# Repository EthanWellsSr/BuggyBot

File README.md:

# BuggyBot

University of Houston–Clear Lake (UHCL) Senior Project, CENG 4265. The course
deliverables use the project title **Self Driving RC Car**; BuggyBot is the
repository and vehicle name.

BuggyBot is an autonomous car project intended to follow a controlled course and obey
traffic signs. The fall scope is a stationary sign-recognition system; the
spring scope is the autonomous vehicle.

## Current state

- The bench platform uses a Raspberry Pi Compute Module 5 (CM5) on its IO Board,
  booting Raspberry Pi OS Lite from an M.2 NVMe SSD. USB Wi-Fi supplies network
  access because this CM5 Lite has no onboard wireless.
- [`Model Training/OpenCV/pi_sign_detection_demo.py`](Model%20Training/OpenCV/)
  is the live sign demo on the CM5. It finds sign regions with OpenCV,
  classifies them with the combined model, and shows the confirmed sign on the
  LCD. In the final test, 60 of 60 LCD outputs were correct (10 printed sign
  classes, 3 times each over two runs, one room).
- [`Hardware/scripts/test_components.py`](Hardware/scripts/test_components.py)
  and [`Hardware/scripts/stress_test.py`](Hardware/scripts/stress_test.py) are
  the hardware integration tests: each device on its own, then
  everything at once. On 10/28 all seven stages of the original combined test passed
  on the Cokoino HAT (pins, I²C, line sensors, IMU, motors, sign pipeline, and a
  120 s stress run with everything at once), powered from the Pi with the wheels
  off the ground. On 11/02 the 120 s stress run passed again with the motors on
  real power (a 9 V bench supply into the Cokoino HAT): no under-voltage, no I²C
  or line-sensor noise, and 30 fps. For the Semester 1 demo, Ethan Bishop's own
  battery runs the CM5, camera, LCD, and travel router, so the demo is mobile
  and reachable over SSH. Motors on battery power and a loaded drivetrain are
  untested. Reports are
  in [`Hardware/integration_reports/`](Hardware/integration_reports/). Nothing
  drives the vehicle yet.
- TensorFlow classifiers have been trained on GTSRB, LISA, Mapillary, and a
  combined LISA+Mapillary dataset. Their models and results are in this repo.
- A ROS 2 node architecture for the vehicle (camera, sign detector, line sensor,
  IMU, behavior, motor driver, LCD, teleop) has been drafted. ROS 2 is installed
  under WSL on a development machine. A preliminary ROS 2 version of the sign
  pipeline (camera, sign classifier, and LCD nodes) runs in Docker on a
  development machine; it is not in this repository and has not run on the CM5.

## Hardware

- **Compute and storage:** Raspberry Pi CM5 (4 GB Lite), CM5 IO Board, M.2 NVMe
- **Networking:** USB Wi-Fi dongle for headless SSH
- **Vision and sensing:** Camera Module 3, ICM-20948 IMU (the HC-SR04 ultrasonic sensor is no longer used)
- **Course sensing:** TCRT5000 IR line sensors (received); a line-sensor script that
  reads the left (GPIO20) and right (GPIO21) sensors is in `Hardware/scripts/Line Sensors.py`
- **Output and motion:** I²C LCD; two motor-controller HATs are supported: the
  Waveshare Motor Driver HAT (2WD, I²C) and the Cokoino 4WD Robot HAT (GPIO).
  Vehicle motor control is being developed
- **Chassis:** EMOZNY Emo smart robot car chassis kit (2 DC gear motors with
  speed encoders, battery box) has been received
- **Custom PCB:** a KiCad carrier-board design, derived from the CM5 IO Board, is
  complete in [`Hardware/BuggyBot KiCAD/`](Hardware/BuggyBot%20KiCAD/), with
  Gerber, BOM, and pick-and-place files (11/03). PCBWay quoted $583 to
  manufacture it, so it will not be made; BuggyBot uses the stock CM5 IO Board

The [parts list](Hardware/partslist.md) records purchase and availability
status. Wiring references and hardware test scripts are in [`Hardware/`](Hardware/);
see its [README](Hardware/README.md).

## Traffic-sign models

The image classifiers use 32×32 sign crops. On the CM5, the live demo in
[`Model Training/OpenCV/`](Model%20Training/OpenCV/README.md) locates signs in
each camera frame, crops them without using the known class, and runs the
combined TFLite model on each crop.

| Dataset and model | Classes | Prepared crops | Held-out result | Status |
| --- | ---: | ---: | --- | --- |
| GTSRB, German signs | 43 | See [training guide](Model%20Training/README.md) | 95.79% top-1 on 12,630 test images | Model and evaluation committed |
| LISA, selected US signs | 12 | 6,097 | 89.90% top-1 on 584 test crops | Model and report committed |
| Mapillary, mapped to the same 12 classes | 12 | 3,449 | 92.59% top-1 on 432 test crops | Model and report committed |
| Combined LISA+Mapillary | 12 | 9,546 | 99.31% top-1 on 1,016 combined test crops | Model, training report, and same-set comparison committed |

The separate LISA and Mapillary percentages use **different test sets** and do
not rank those models. The [same-set comparison](Model%20Training/reports/combined_model_comparison.md)
evaluates all three US-sign models on the 1,016 combined test crops. The
combined set preserves each source's split but does not establish physical-sign
independence across datasets. The Mapillary test set has only two speed-limit-65
crops.

On BuggyBot's own camera, the combined model classified **all 329** cropped
photos of the printed [sign cards](Sign%20Cards/README.md) correctly (10
classes, three lighting conditions, about 30 distinct setups). The LISA and
Mapillary models scored 47.7% and 79.9%. These crops were placed with
knowledge of each sign's class. Through the car's own detector (the live
demo), 60 of 60 LCD outputs were correct in one room; distance, angle, other
lighting are still unmeasured; CM5 inference averaged 1.9 ms per crop (36 fps). See the [model training guide](Model%20Training/README.md) for the
scripts, preparation steps, and detailed results.

## Team

- Ethan Wells (Group Leader)
- Alexis Perez
- Ethan Bishop
- Abigail Duran

**Faculty advisor:** Dr. Nguyen · **TA:** Ruben Ramirez

## Repository layout

| Path | Contents |
| --- | --- |
| `Proposal/` | Project proposal and Gantt charts |
| `Semester 1 Deliverables/` | Final Semester 1 deliverables: poster, final presentation, Project Report, and Technical Paper |
| `Weekly Reports/` | Rolling report and presentation, source slides, build scripts, and frozen weekly deliverables |
| `Hardware/` | Parts list, wiring references, hardware test scripts, integration test reports, and the KiCad custom-PCB project |
| `Model Training/` | GTSRB, LISA, Mapillary, and combined-data preparation, training, evaluation, and reports; the live Pi sign demo in `OpenCV/`; downloaded datasets are Git ignored |
| `Sign Cards/` | Printable 3 x 5 inch cards for the 12 U.S. sign classes, a US Letter print sheet, and cropped camera test photos |
| `Learning/` | Self-directed learning side-quests, separate from the main project |
| `setup.sh` | Installs Git, Python, pip, and venv on your development computer |
| `Hardware/setup.sh` | Installs Picamera2, OpenCV, NumPy, SMBus, GPIOZero, and the LiteRT venv on BuggyBot (the CM5) |
| `AGENTS.md` | Working agreements for AI assistants used on this repo |
| `.github/` | GitHub Actions CI, run on every push: Python scripts compile, `ruff` bug lint, sign-demo regression on the 329 test crops, integration-test pin map for both motor HATs, and Markdown link check (helper scripts in `.github/scripts/`) |

### Weekly reports

Weekly reports and the presentation deck are built from `Weekly Reports/`;
see [`Weekly Reports/context.md`](Weekly%20Reports/context.md) for the build
and format guide, and [`slides/README.md`](Weekly%20Reports/slides/README.md)
for how each person edits their own slides.

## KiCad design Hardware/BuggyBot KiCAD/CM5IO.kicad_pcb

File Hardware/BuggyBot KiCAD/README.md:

# BuggyBot KiCad Hardware Files

This folder contains the KiCad design files used for the BuggyBot senior capstone project.

The design started from the Raspberry Pi Compute Module 5 IO Board files and was modified into the custom BuggyBot carrier PCB. Abigail Duran completed the layout and generated the manufacturing files in Week 11 (11/03/2026), and Ethan Wells gave final approval to send it for manufacturing. After PCBWay quoted $583, the team decided not to manufacture it.

## Main Project Files

- `CM5IO.kicad_pro`  
  Main KiCad project file. Open this file first to load the complete project.

- `CM5IO.kicad_sch`  
  Main schematic, inherited from the CM5 IO Board.

- `CM5IO.kicad_pcb`  
  PCB layout for BuggyBot: 4 layers, 1.6 mm FR-4. Earlier layouts,
  including the 10/23 redesign file, are in Git history.

- `CM5IO.kicad_sym`  
  Custom symbol library used by the project.

## Additional Schematic Sheets

- `CM5_GPIO.kicad_sch`  
  GPIO-related circuitry, including the BuggyBot additions: 4-pin quick-connect
  ports for the IMU (J3) and the LCD (J4).

- `CM5_HighSpeed.kicad_sch`  
  High-speed interfaces and related circuitry.

- `PCIe-M2.kicad_sch`  
  PCIe and M.2 circuitry.

## Libraries

- `CM5IO.pretty/`  
  Custom KiCad footprint library.

- `Image.pretty/`  
  BuggyBot ladybug logo footprints for the silkscreen.

- `CM5IO.3dshapes/`  
  3D models used by PCB footprints.

- `fp-lib-table`  
  KiCad footprint library configuration.

- `sym-lib-table`  
  KiCad symbol library configuration.

## Manufacturing Files (`PCBWay/`)

- `Gerbers/`  
  Gerber files for each copper, mask, paste, silkscreen, and edge-cut layer,
  the plated and non-plated drill files, and the Gerber job file.

- `Gerbers.zip`  
  The same Gerber and drill files in one archive for upload to the board house.

- `Gerbers/IMPEDANCE_CONTROL.txt`  
  Stackup and controlled-impedance requirements for the board house
  (100 Ω and 90 Ω differential pairs, 50 Ω single-ended).

- `BuggyBotBOM.xlsx`  
  Bill of materials for the BuggyBot board.

- `CM5IO-all-pos.csv`  
  Pick-and-place (component position) file for assembly.

## Other Files

- `CM5IOBOM.txt`  
  Bill of Materials from the original CM5 IO Board design.

## Opening the Project

1. Install KiCad 10 or a compatible newer version.
2. Clone or download the BuggyBot repository.
3. Navigate to:

   `Hardware/BuggyBot KiCAD`

4. Open:

   `CM5IO.kicad_pro`

Opening the `.kicad_pro` file should load the schematic, PCB, and associated project libraries.

## Project Purpose

These files are the final design for BuggyBot's custom PCB. PCBWay quoted $583 to manufacture and assemble it (after a discount), which the team judged not financially feasible. The board will not be manufactured; BuggyBot uses the stock CM5 IO Board.

The original CM5 IO Board contains some different hardware than BuggyBot requires. In October 2026 the team reviewed which CM5 support circuitry and interfaces to keep, removing the second HDMI port, the second camera/display connector, and the microSD slot, and added quick-connect headers for BuggyBot's sensors and display: the IMU (J3, 10/14), the LCD (J4, 10/22), and the two line sensors (J6 and J7, 10/23). The component checklist from that review is not committed to this repository.

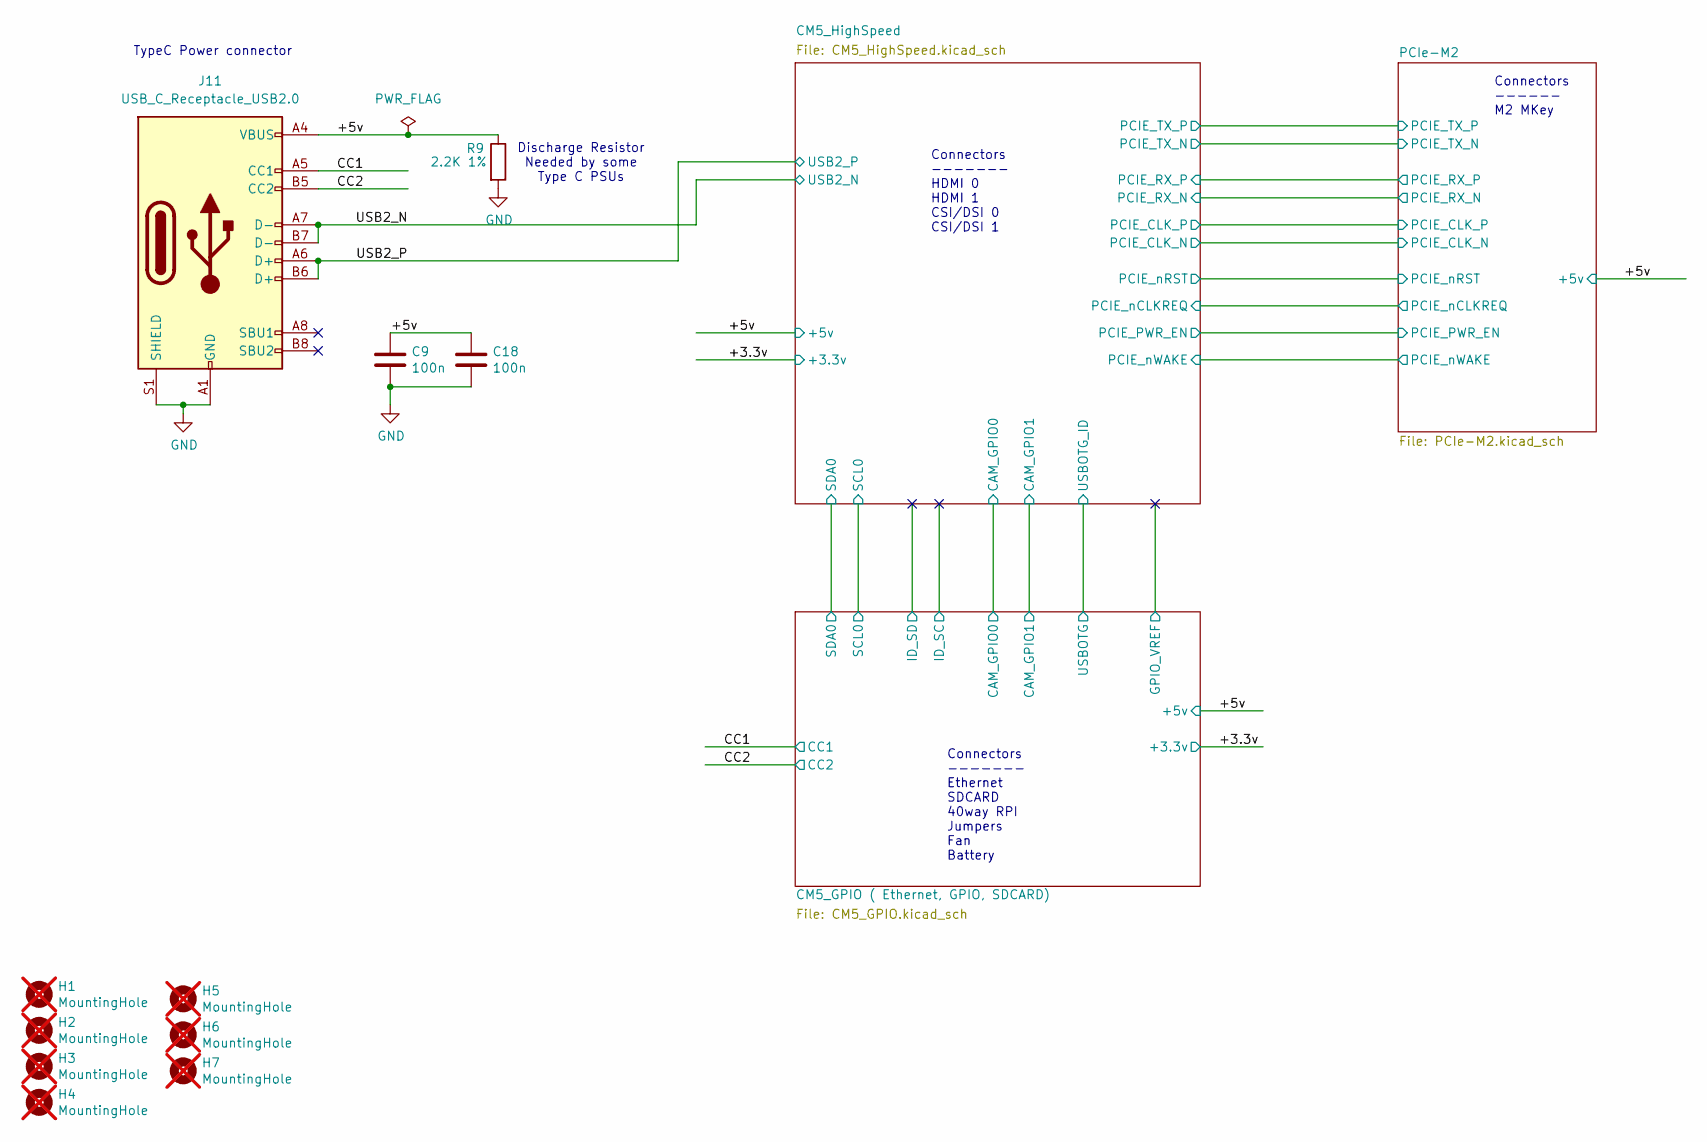
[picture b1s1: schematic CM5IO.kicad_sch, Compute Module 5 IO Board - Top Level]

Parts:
C9, C18: 100n; C_0402_1005Metric; Part Description 0.1uF 10% 16V Ceramic Capacitor X7R 040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
H1, H2, H3, H4, H5, H6, H7: MountingHole; MountingHole_2.7mm_M2.5_DIN965; Part Description M2.5 mounting hole; not fitted
J11: USB_C_Receptacle_USB2.0; USB_C_Receptacle_GCT_USB4105-xx-A_16P_TopMnt_Horizontal; Part Description USBC USB2 data and power connector
R9: 2.2K 1%; R_0402_1005Metric; Part Description Resistor 2.2K M1005 1% 63mW

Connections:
/+5v: C9.1, C18.1, J11.A4 (VBUS), J11.A9 (VBUS), J11.B4 (VBUS), J11.B9 (VBUS), R9.1; also elsewhere on the board
/CC1: J11.A5 (CC1); also elsewhere on the board
/CC2: J11.B5 (CC2); also elsewhere on the board
/USB2_N: J11.A7 (D-), J11.B7 (D-); also elsewhere on the board
/USB2_P: J11.A6 (D+), J11.B6 (D+); also elsewhere on the board
GND: C9.2, C18.2, J11.A1 (GND), J11.A12 (GND), J11.B1 (GND), J11.B12 (GND), J11.S1 (SHIELD), R9.2; also elsewhere on the board

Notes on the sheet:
Connectors ------- Ethernet SDCARD 40way RPI Jumpers Fan Battery
Connectors ------ M2 MKey
Discharge Resistor Needed by some Type C PSUs
TypeC Power connector
Connectors ------- HDMI 0 HDMI 1 CSI/DSI 0 CSI/DSI 1

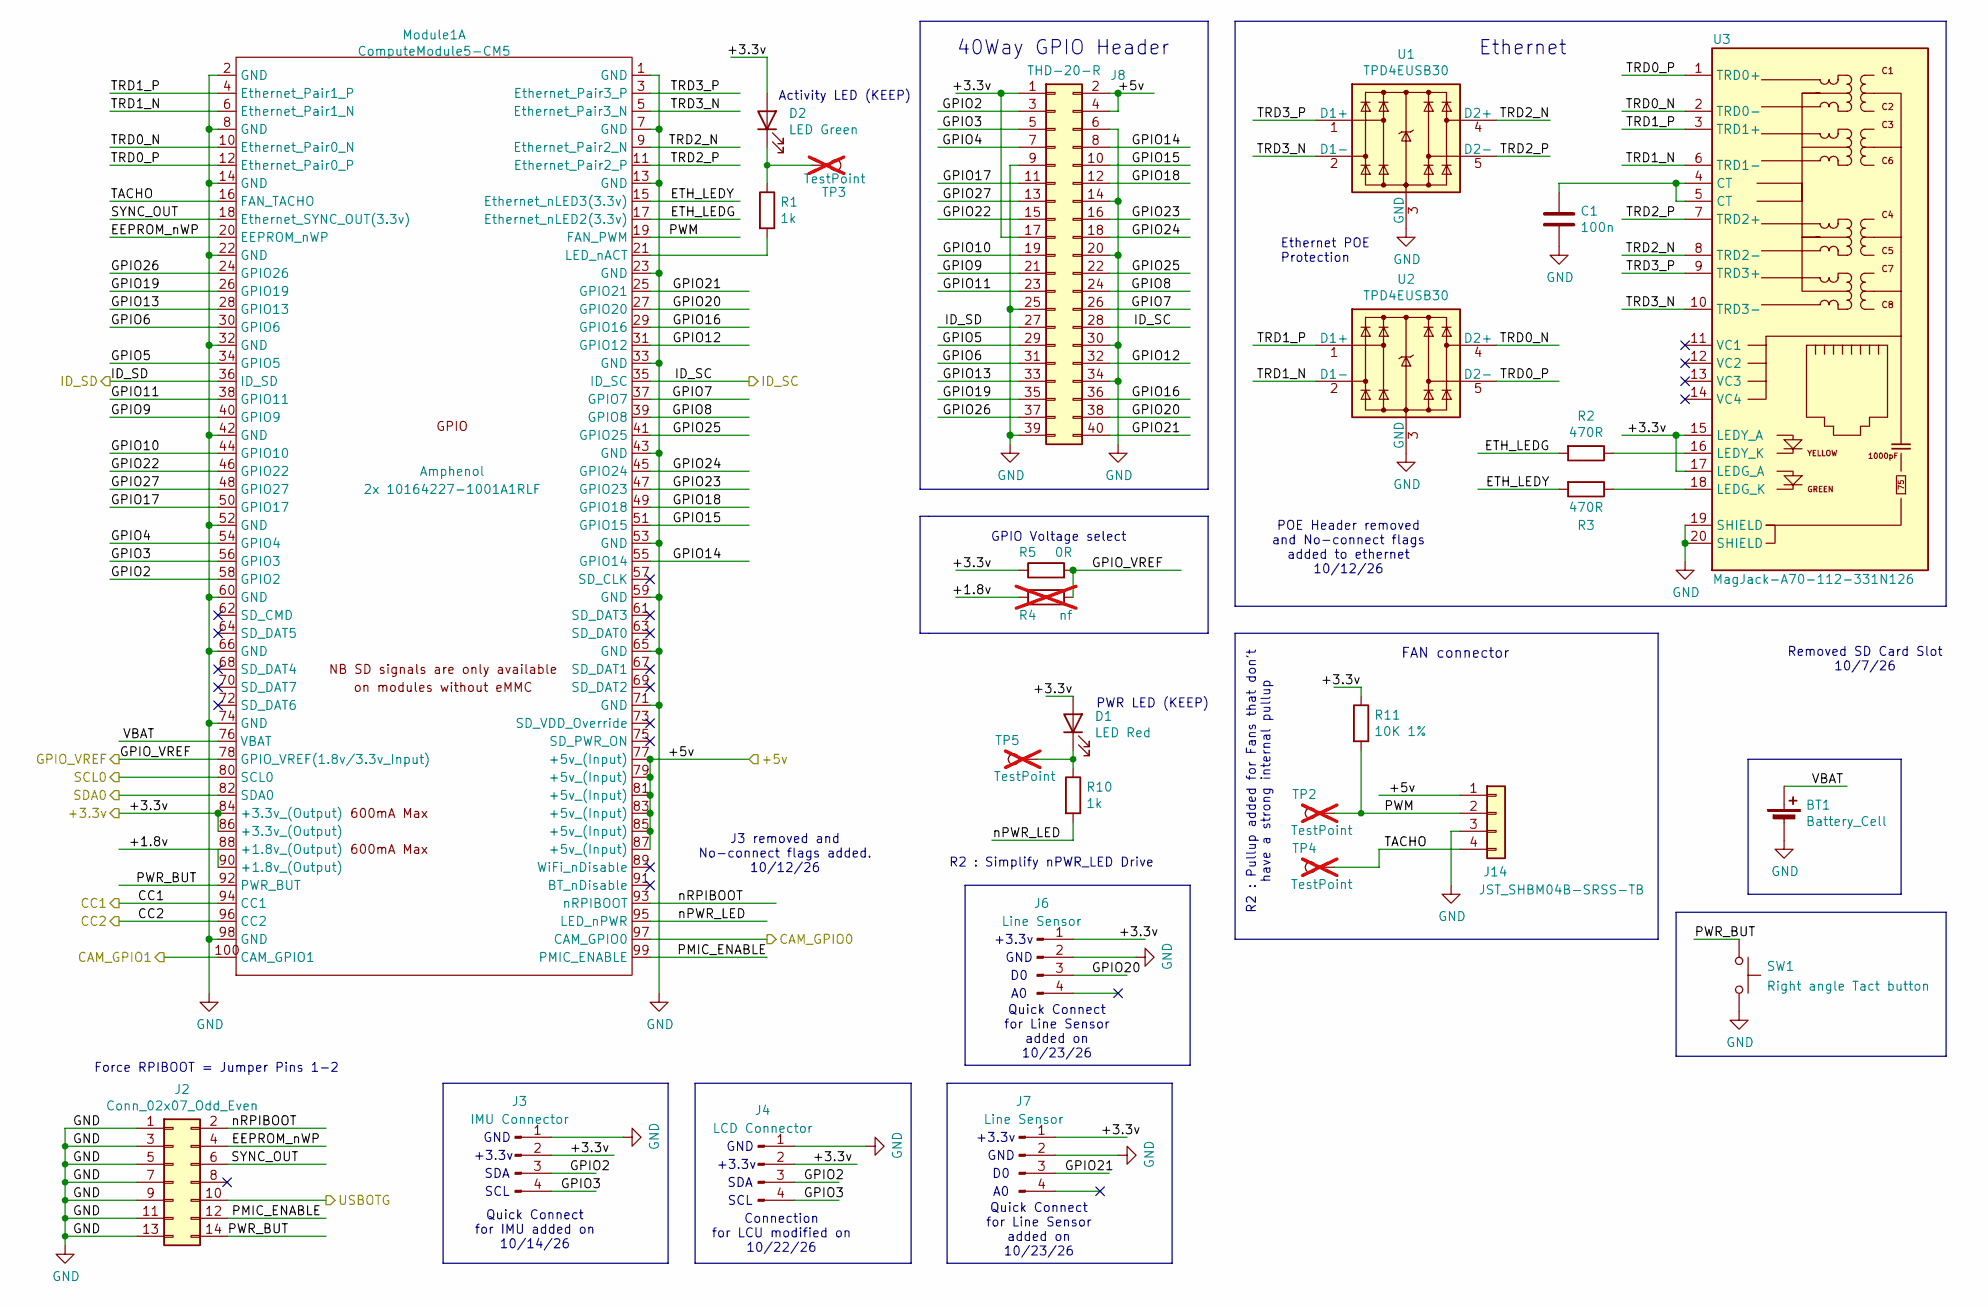
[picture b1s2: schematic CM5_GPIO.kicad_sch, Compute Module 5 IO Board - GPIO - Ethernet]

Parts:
BT1: Battery_Cell; BatteryHolder_Keystone_3034_1x20mm; Part Description Battery Retainer Coin, 20.0mm 1 Cell SM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
C1: 100n; C_0402_1005Metric; Part Description 0.1uF 10% 16V Ceramic Capacitor X7R 040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
D1: LED Red; LED_0603_1608Metric; Part Description Red 620nm LED Indication - Discrete 2.2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
D2: LED Green; LED_0603_1608Metric; Part Description Green 572nm LED Indication - Discrete 2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
J2: Conn_02x07_Odd_Even; PinHeader_2x07_P2.54mm_Vertical; Part Description PinHeader_2x07_P2.54mm_Vertical
J3: IMU Connector; JST_SH_SM04B-SRSS-TB_1x04-1MP_P1.00mm_Horizontal
J4: LCD Connector; JST_SH_SM04B-SRSS-TB_1x04-1MP_P1.00mm_Horizontal
J6, J7: Line Sensor; JST_SH_SM04B-SRSS-TB_1x04-1MP_P1.00mm_Horizontal
J8: THD-20-R; PinHeader_2x20_P2.54mm_Vertical; Part Description PinHeader_2x20_P2.54mm_Vertical
J14: JST_SHBM04B-SRSS-TB; JST_SH_BM04B-SRSS-TB_1x04-1MP_P1.00mm_Vertical; Part Description 4 pin vertical 1mm pitch connector
Module1: ComputeModule5-CM5; Raspberry-Pi-5-Compute-Module; Part Description 2 pcs per board
R1, R10: 1k; R_0402_1005Metric; Part Description Resistor 1K M1005 1% 63mW
R2, R3: 470R; R_0402_1005Metric; Part Description Resistor 470R M1005 1% 63mW
R4: nf; R_0805_2012Metric_Pad1.20x1.40mm_HandSolder; not fitted
R5: 0R; R_0805_2012Metric_Pad1.20x1.40mm_HandSolder; Part Description Resistor 0R M2012 5%
R11: 10K 1%; R_0402_1005Metric; Part Description Resistor 10K M1005 1% 63mW
SW1: Right angle Tact button; SW_Tactile_SPST_Angled_PTS645Vx58-2LFS; Part Description Right angle through hole Tact switch
TP2, TP3, TP4, TP5: TestPoint; TestPoint_Pad_2.0x2.0mm; Part Description Test point; not fitted
U1, U2: TPD4EUSB30; USON-10_2.5x1.0mm_P0.5mm; Part Description Quad TVS diode for high speed signals (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
U3: MagJack-A70-112-331N126; TRJG0926HENL; Part Description Gigabit Ethernet Magjack

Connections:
/+3.3v: D1.2 (A), D2.2 (A), J3.2, J4.2, J6.1, J7.1, J8.1, J8.17, Module1.84 (+3.3v_(Output)), Module1.86 (+3.3v_(Output)), R5.1, R11.1, U3.15 (LEDY_A), U3.17 (LEDG_A); also elsewhere on the board
/+5v: J8.2, J8.4, J14.1, Module1.77 (+5v_(Input)), Module1.79 (+5v_(Input)), Module1.81 (+5v_(Input)), Module1.83 (+5v_(Input)), Module1.85 (+5v_(Input)), Module1.87 (+5v_(Input)); also elsewhere on the board
/CC1: Module1.94 (CC1); also elsewhere on the board
/CC2: Module1.96 (CC2); also elsewhere on the board
/CM5_GPIO ( Ethernet, GPIO, SDCARD)/+1.8v: Module1.88 (+1.8v_(Output)), Module1.90 (+1.8v_(Output)), R4.1
/CM5_GPIO ( Ethernet, GPIO, SDCARD)/CAM_GPIO0: Module1.97 (CAM_GPIO0); also elsewhere on the board
/CM5_GPIO ( Ethernet, GPIO, SDCARD)/CAM_GPIO1: Module1.100 (CAM_GPIO1); also elsewhere on the board
/CM5_GPIO ( Ethernet, GPIO, SDCARD)/EEPROM_nWP: J2.4, Module1.20 (EEPROM_nWP)
/CM5_GPIO ( Ethernet, GPIO, SDCARD)/ETH_LEDG: Module1.17 (Ethernet_nLED2(3.3v)), R2.2
/CM5_GPIO ( Ethernet, GPIO, SDCARD)/ETH_LEDY: Module1.15 (Ethernet_nLED3(3.3v)), R3.2
/CM5_GPIO ( Ethernet, GPIO, SDCARD)/GPIO2: J3.3, J4.3, J8.3, Module1.58 (GPIO2)
/CM5_GPIO ( Ethernet, GPIO, SDCARD)/GPIO3: J3.4, J4.4, J8.5, Module1.56 (GPIO3)
/CM5_GPIO ( Ethernet, GPIO, SDCARD)/GPIO4: J8.7, Module1.54 (GPIO4)
/CM5_GPIO ( Ethernet, GPIO, SDCARD)/GPIO5: J8.29, Module1.34 (GPIO5)
/CM5_GPIO ( Ethernet, GPIO, SDCARD)/GPIO6: J8.31, Module1.30 (GPIO6)
/CM5_GPIO ( Ethernet, GPIO, SDCARD)/GPIO7: J8.26, Module1.37 (GPIO7)
/CM5_GPIO ( Ethernet, GPIO, SDCARD)/GPIO8: J8.24, Module1.39 (GPIO8)
/CM5_GPIO ( Ethernet, GPIO, SDCARD)/GPIO9: J8.21, Module1.40 (GPIO9)
/CM5_GPIO ( Ethernet, GPIO, SDCARD)/GPIO10: J8.19, Module1.44 (GPIO10)
/CM5_GPIO ( Ethernet, GPIO, SDCARD)/GPIO11: J8.23, Module1.38 (GPIO11)
/CM5_GPIO ( Ethernet, GPIO, SDCARD)/GPIO12: J8.32, Module1.31 (GPIO12)
/CM5_GPIO ( Ethernet, GPIO, SDCARD)/GPIO13: J8.33, Module1.28 (GPIO13)
/CM5_GPIO ( Ethernet, GPIO, SDCARD)/GPIO14: J8.8, Module1.55 (GPIO14)
/CM5_GPIO ( Ethernet, GPIO, SDCARD)/GPIO15: J8.10, Module1.51 (GPIO15)
/CM5_GPIO ( Ethernet, GPIO, SDCARD)/GPIO16: J8.36, Module1.29 (GPIO16)
/CM5_GPIO ( Ethernet, GPIO, SDCARD)/GPIO17: J8.11, Module1.50 (GPIO17)
/CM5_GPIO ( Ethernet, GPIO, SDCARD)/GPIO18: J8.12, Module1.49 (GPIO18)
/CM5_GPIO ( Ethernet, GPIO, SDCARD)/GPIO19: J8.35, Module1.26 (GPIO19)
/CM5_GPIO ( Ethernet, GPIO, SDCARD)/GPIO20: J6.3, J8.38, Module1.27 (GPIO20)
/CM5_GPIO ( Ethernet, GPIO, SDCARD)/GPIO21: J7.3, J8.40, Module1.25 (GPIO21)
/CM5_GPIO ( Ethernet, GPIO, SDCARD)/GPIO22: J8.15, Module1.46 (GPIO22)
/CM5_GPIO ( Ethernet, GPIO, SDCARD)/GPIO23: J8.16, Module1.47 (GPIO23)
/CM5_GPIO ( Ethernet, GPIO, SDCARD)/GPIO24: J8.18, Module1.45 (GPIO24)
/CM5_GPIO ( Ethernet, GPIO, SDCARD)/GPIO25: J8.22, Module1.41 (GPIO25)
/CM5_GPIO ( Ethernet, GPIO, SDCARD)/GPIO26: J8.37, Module1.24 (GPIO26)
/CM5_GPIO ( Ethernet, GPIO, SDCARD)/GPIO27: J8.13, Module1.48 (GPIO27)
/CM5_GPIO ( Ethernet, GPIO, SDCARD)/GPIO_VREF: Module1.78 (GPIO_VREF(1.8v/3.3v_Input)), R4.2, R5.2
/CM5_GPIO ( Ethernet, GPIO, SDCARD)/ID_SC: J8.28, Module1.35 (ID_SC)
/CM5_GPIO ( Ethernet, GPIO, SDCARD)/ID_SD: J8.27, Module1.36 (ID_SD)
/CM5_GPIO ( Ethernet, GPIO, SDCARD)/PMIC_ENABLE: J2.12, Module1.99 (PMIC_ENABLE)
/CM5_GPIO ( Ethernet, GPIO, SDCARD)/PWM: J14.2, Module1.19 (FAN_PWM), R11.2, TP2.1 (1_1)
/CM5_GPIO ( Ethernet, GPIO, SDCARD)/PWR_BUT: J2.14, Module1.92 (PWR_BUT), SW1.1
/CM5_GPIO ( Ethernet, GPIO, SDCARD)/SYNC_OUT: J2.6, Module1.18 (Ethernet_SYNC_OUT(3.3v))
/CM5_GPIO ( Ethernet, GPIO, SDCARD)/TACHO: J14.4, Module1.16 (FAN_TACHO), TP4.1 (1_1)
/CM5_GPIO ( Ethernet, GPIO, SDCARD)/TRD0_N: Module1.10 (Ethernet_Pair0_N), U2.4 (D2+), U2.7, U3.2 (TRD0-)
/CM5_GPIO ( Ethernet, GPIO, SDCARD)/TRD0_P: Module1.12 (Ethernet_Pair0_P), U2.5 (D2-), U2.6, U3.1 (TRD0+)
/CM5_GPIO ( Ethernet, GPIO, SDCARD)/TRD1_N: Module1.6 (Ethernet_Pair1_N), U2.2 (D1-), U2.9, U3.6 (TRD1-)
/CM5_GPIO ( Ethernet, GPIO, SDCARD)/TRD1_P: Module1.4 (Ethernet_Pair1_P), U2.1 (D1+), U2.10, U3.3 (TRD1+)
/CM5_GPIO ( Ethernet, GPIO, SDCARD)/TRD2_N: Module1.9 (Ethernet_Pair2_N), U1.4 (D2+), U1.7, U3.8 (TRD2-)
/CM5_GPIO ( Ethernet, GPIO, SDCARD)/TRD2_P: Module1.11 (Ethernet_Pair2_P), U1.5 (D2-), U1.6, U3.7 (TRD2+)
/CM5_GPIO ( Ethernet, GPIO, SDCARD)/TRD3_N: Module1.5 (Ethernet_Pair3_N), U1.2 (D1-), U1.9, U3.10 (TRD3-)
/CM5_GPIO ( Ethernet, GPIO, SDCARD)/TRD3_P: Module1.3 (Ethernet_Pair3_P), U1.1 (D1+), U1.10, U3.9 (TRD3+)
/CM5_GPIO ( Ethernet, GPIO, SDCARD)/USBOTG: J2.10; also elsewhere on the board
/CM5_GPIO ( Ethernet, GPIO, SDCARD)/VBAT: BT1.1 (+), Module1.76 (VBAT)
/CM5_GPIO ( Ethernet, GPIO, SDCARD)/nPWR_LED: Module1.95 (LED_nPWR), R10.2
/CM5_GPIO ( Ethernet, GPIO, SDCARD)/nRPIBOOT: J2.2, Module1.93 (nRPIBOOT)
/CM5_HighSpeed/SCL0: Module1.80 (SCL0); also elsewhere on the board
/CM5_HighSpeed/SDA0: Module1.82 (SDA0); also elsewhere on the board
GND: BT1.2 (-), C1.2, J2.1, J2.3, J2.5, J2.7, J2.9, J2.11, J2.13, J3.1, J4.1, J6.2, J7.2, J8.6, J8.9, J8.14, J8.20, J8.25, J8.30, J8.34, J8.39, J14.3, Module1.1 (GND), Module1.2 (GND), Module1.7 (GND), Module1.8 (GND), Module1.13 (GND), Module1.14 (GND), Module1.22 (GND), Module1.23 (GND), Module1.32 (GND), Module1.33 (GND), Module1.42 (GND), Module1.43 (GND), Module1.52 (GND), Module1.53 (GND), Module1.59 (GND), Module1.60 (GND), Module1.65 (GND), Module1.66 (GND), Module1.71 (GND), Module1.74 (GND), Module1.98 (GND), SW1.2, U1.3 (GND), U1.8 (GND), U2.3 (GND), U2.8 (GND), U3.19 (SHIELD), U3.20 (SHIELD); also elsewhere on the board
unnamed: C1.1, U3.4 (CT), U3.5 (CT)
unnamed: D1.1 (K), R10.1, TP5.1 (1_1)
unnamed: D2.1 (K), R1.1, TP3.1 (1_1)
unnamed: Module1.21 (LED_nACT), R1.2
unnamed: R3.1, U3.18 (LEDG_K)
unnamed: R2.1, U3.16 (LEDY_K)

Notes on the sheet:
Quick Connect for Line Sensor added on 10/23/26
+3.3v
GND
SDA
40Way GPIO Header
Activity LED (KEEP)
R2 : Simplify nPWR_LED Drive
FAN connector
J3 removed and No-connect flags added. 10/12/26
Quick Connect for IMU added on 10/14/26
Removed SD Card Slot 10/7/26
Ethernet POE Protection
GPIO Voltage select
SCL
R2 : Pullup added for Fans that don't have a strong internal pullup
POE Header removed and No-connect flags added to ethernet 10/12/26
Force RPIBOOT = Jumper Pins 1-2
PWR LED (KEEP)
Connection for LCU modified on 10/22/26
Ethernet

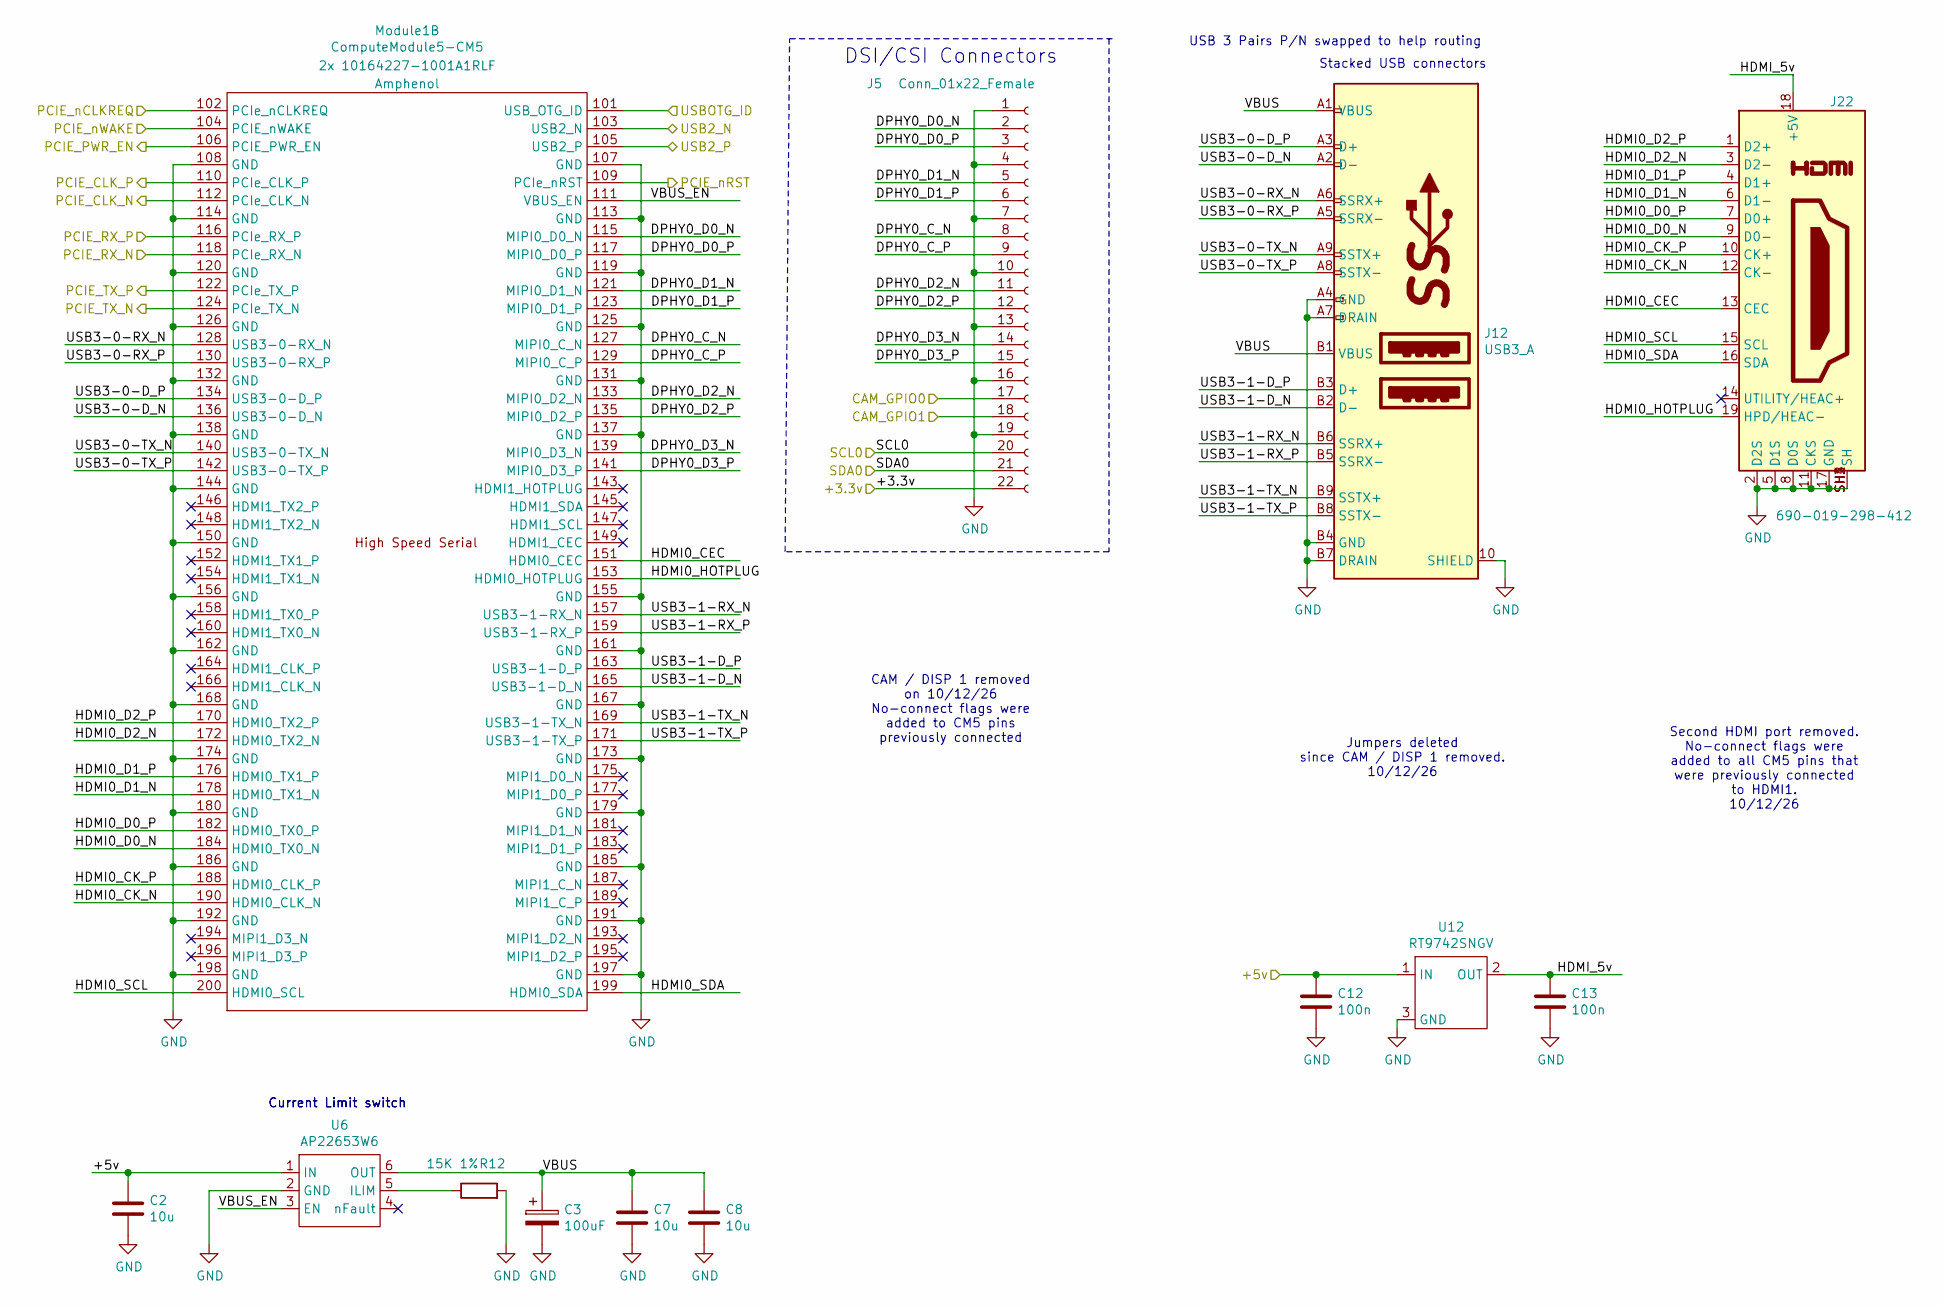
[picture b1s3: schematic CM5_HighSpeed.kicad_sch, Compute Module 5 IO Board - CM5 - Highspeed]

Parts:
C2, C7, C8: 10u; C_0805_2012Metric; Part Description 10uF 10% 10V Ceramic Capacitor X7R 0805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
C3: 100uF; CP_EIA-7343-31_Kemet-D; Part Description Capacitor, SP-Cap, 100u, 6.3V, 15mR ESR
C12, C13: 100n; C_0402_1005Metric; Part Description 0.1uF 10% 16V Ceramic Capacitor X7R 040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
J5: Conn_01x22_Female; Hirose_FH12-22S-0.5SH_1x22-1MP_P0.50mm_Horizontal; Part Description 22 Position FFC, FPC Connector Contacts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
J12: USB3_A; MTCONN_UBAF30-D2011; Part Description Dual USB 3 connector
J22: 690-019-298-412; EDAC 690-019-298-412; Part Description HDMI Connector, Right Angle, 19 Contact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
Module1: ComputeModule5-CM5; Raspberry-Pi-5-Compute-Module; Part Description 2 pcs per board
R12: 15K 1%; R_0402_1005Metric; Part Description Resistor 15K M1005 1% 63mW
U6: AP22653W6; SOT-23-6; Part Description Power Switch/Driver 1:1 P-Channel 2.1A 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
U12: RT9742SNGV; TSOT-23_HandSoldering; Part Description Power Switch/Driver 1:1 N-Channel 500mA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

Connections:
/+3.3v: J5.22; also elsewhere on the board
/+5v: C2.1, C12.1, U6.1 (IN), U12.1 (IN); also elsewhere on the board
/CM5_GPIO ( Ethernet, GPIO, SDCARD)/CAM_GPIO0: J5.17; also elsewhere on the board
/CM5_GPIO ( Ethernet, GPIO, SDCARD)/CAM_GPIO1: J5.18; also elsewhere on the board
/CM5_GPIO ( Ethernet, GPIO, SDCARD)/USBOTG: Module1.101 (USB_OTG_ID); also elsewhere on the board
/CM5_HighSpeed/DPHY0_C_N: J5.8, Module1.127 (MIPI0_C_N)
/CM5_HighSpeed/DPHY0_C_P: J5.9, Module1.129 (MIPI0_C_P)
/CM5_HighSpeed/DPHY0_D0_N: J5.2, Module1.115 (MIPI0_D0_N)
/CM5_HighSpeed/DPHY0_D0_P: J5.3, Module1.117 (MIPI0_D0_P)
/CM5_HighSpeed/DPHY0_D1_N: J5.5, Module1.121 (MIPI0_D1_N)
/CM5_HighSpeed/DPHY0_D1_P: J5.6, Module1.123 (MIPI0_D1_P)
/CM5_HighSpeed/DPHY0_D2_N: J5.11, Module1.133 (MIPI0_D2_N)
/CM5_HighSpeed/DPHY0_D2_P: J5.12, Module1.135 (MIPI0_D2_P)
/CM5_HighSpeed/DPHY0_D3_N: J5.14, Module1.139 (MIPI0_D3_N)
/CM5_HighSpeed/DPHY0_D3_P: J5.15, Module1.141 (MIPI0_D3_P)
/CM5_HighSpeed/HDMI0_CEC: J22.13 (CEC), Module1.151 (HDMI0_CEC)
/CM5_HighSpeed/HDMI0_CK_N: J22.12 (CK-), Module1.190 (HDMI0_CLK_N)
/CM5_HighSpeed/HDMI0_CK_P: J22.10 (CK+), Module1.188 (HDMI0_CLK_P)
/CM5_HighSpeed/HDMI0_D0_N: J22.9 (D0-), Module1.184 (HDMI0_TX0_N)
/CM5_HighSpeed/HDMI0_D0_P: J22.7 (D0+), Module1.182 (HDMI0_TX0_P)
/CM5_HighSpeed/HDMI0_D1_N: J22.6 (D1-), Module1.178 (HDMI0_TX1_N)
/CM5_HighSpeed/HDMI0_D1_P: J22.4 (D1+), Module1.176 (HDMI0_TX1_P)
/CM5_HighSpeed/HDMI0_D2_N: J22.3 (D2-), Module1.172 (HDMI0_TX2_N)
/CM5_HighSpeed/HDMI0_D2_P: J22.1 (D2+), Module1.170 (HDMI0_TX2_P)
/CM5_HighSpeed/HDMI0_HOTPLUG: J22.19 (HPD/HEAC-), Module1.153 (HDMI0_HOTPLUG)
/CM5_HighSpeed/HDMI0_SCL: J22.15 (SCL), Module1.200 (HDMI0_SCL)
/CM5_HighSpeed/HDMI0_SDA: J22.16 (SDA), Module1.199 (HDMI0_SDA)
/CM5_HighSpeed/HDMI_5v: C13.1, J22.18 (+5V), U12.2 (OUT)
/CM5_HighSpeed/PCIE_CLK_N: Module1.112 (PCIe_CLK_N); also elsewhere on the board
/CM5_HighSpeed/PCIE_CLK_P: Module1.110 (PCIe_CLK_P); also elsewhere on the board
/CM5_HighSpeed/PCIE_PWR_EN: Module1.106 (PCIE_PWR_EN); also elsewhere on the board
/CM5_HighSpeed/PCIE_RX_N: Module1.118 (PCIe_RX_N); also elsewhere on the board
/CM5_HighSpeed/PCIE_RX_P: Module1.116 (PCIe_RX_P); also elsewhere on the board
/CM5_HighSpeed/PCIE_TX_N: Module1.124 (PCIe_TX_N); also elsewhere on the board
/CM5_HighSpeed/PCIE_TX_P: Module1.122 (PCIe_TX_P); also elsewhere on the board
/CM5_HighSpeed/PCIE_nCLKREQ: Module1.102 (PCIe_nCLKREQ); also elsewhere on the board
/CM5_HighSpeed/PCIE_nRST: Module1.109 (PCIe_nRST); also elsewhere on the board
/CM5_HighSpeed/PCIE_nWAKE: Module1.104 (PCIE_nWAKE); also elsewhere on the board
/CM5_HighSpeed/SCL0: J5.20; also elsewhere on the board
/CM5_HighSpeed/SDA0: J5.21; also elsewhere on the board
/CM5_HighSpeed/USB3-0-D_N: J12.A2 (D-), Module1.136 (USB3-0-D_N)
/CM5_HighSpeed/USB3-0-D_P: J12.A3 (D+), Module1.134 (USB3-0-D_P)
/CM5_HighSpeed/USB3-0-RX_N: J12.A6 (SSRX+), Module1.128 (USB3-0-RX_N)
/CM5_HighSpeed/USB3-0-RX_P: J12.A5 (SSRX-), Module1.130 (USB3-0-RX_P)
/CM5_HighSpeed/USB3-0-TX_N: J12.A9 (SSTX+), Module1.140 (USB3-0-TX_N)
/CM5_HighSpeed/USB3-0-TX_P: J12.A8 (SSTX-), Module1.142 (USB3-0-TX_P)
/CM5_HighSpeed/USB3-1-D_N: J12.B2 (D-), Module1.165 (USB3-1-D_N)
/CM5_HighSpeed/USB3-1-D_P: J12.B3 (D+), Module1.163 (USB3-1-D_P)
/CM5_HighSpeed/USB3-1-RX_N: J12.B6 (SSRX+), Module1.157 (USB3-1-RX_N)
/CM5_HighSpeed/USB3-1-RX_P: J12.B5 (SSRX-), Module1.159 (USB3-1-RX_P)
/CM5_HighSpeed/USB3-1-TX_N: J12.B9 (SSTX+), Module1.169 (USB3-1-TX_N)
/CM5_HighSpeed/USB3-1-TX_P: J12.B8 (SSTX-), Module1.171 (USB3-1-TX_P)
/CM5_HighSpeed/VBUS: C3.1, C7.1, C8.1, J12.A1 (VBUS), J12.B1 (VBUS), U6.6 (OUT)
/CM5_HighSpeed/VBUS_EN: Module1.111 (VBUS_EN), U6.3 (EN)
/USB2_N: Module1.103 (USB2_N); also elsewhere on the board
/USB2_P: Module1.105 (USB2_P); also elsewhere on the board
GND: C2.2, C3.2, C7.2, C8.2, C12.2, C13.2, J5.1, J5.4, J5.7, J5.10, J5.13, J5.16, J5.19, J12.10 (SHIELD), J12.A4 (GND), J12.A7 (DRAIN), J12.B4 (GND), J12.B7 (DRAIN), J22.2 (D2S), J22.5 (D1S), J22.8 (D0S), J22.11 (CKS), J22.17 (GND), J22.SH1 (SH), J22.SH2 (SH), J22.SH3 (SH), J22.SH4 (SH), Module1.107 (GND), Module1.108 (GND), Module1.113 (GND), Module1.114 (GND), Module1.119 (GND), Module1.120 (GND), Module1.125 (GND), Module1.126 (GND), Module1.131 (GND), Module1.132 (GND), Module1.137 (GND), Module1.138 (GND), Module1.144 (GND), Module1.150 (GND), Module1.155 (GND), Module1.156 (GND), Module1.161 (GND), Module1.162 (GND), Module1.167 (GND), Module1.168 (GND), Module1.173 (GND), Module1.174 (GND), Module1.179 (GND), Module1.180 (GND), Module1.185 (GND), Module1.186 (GND), Module1.191 (GND), Module1.192 (GND), Module1.197 (GND), Module1.198 (GND), R12.2, U6.2 (GND), U12.3 (GND); also elsewhere on the board
unnamed: R12.1, U6.5 (ILIM)

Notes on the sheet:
Jumpers deleted since CAM / DISP 1 removed. 10/12/26
USB 3 Pairs P/N swapped to help routing
Current Limit switch
DSI/CSI Connectors
Second HDMI port removed. No-connect flags were added to all CM5 pins that were previously connected to HDMI1. 10/12/26
Stacked USB connectors
CAM / DISP 1 removed on 10/12/26 No-connect flags were added to CM5 pins previously connected
